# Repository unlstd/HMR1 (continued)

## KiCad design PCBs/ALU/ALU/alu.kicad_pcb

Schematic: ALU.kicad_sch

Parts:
C41, C42, C51, C52, C53, C54, C57, C60, C61, C62, C63, C64, C65, C66, C67, C68, C69, C70, C71, C72, C73, C74, C75, C76, C77, C78, C79, C80, C81, C82, C83, C84, C85, C86, C87, C88, C89, C90, C91, C92, C93, C94, C95, C96, C97, C98: 100nF; C_Disc_D3.0mm_W1.6mm_P2.50mm
J1: ALU_DATA; PinHeader_1x33_P2.54mm_Horizontal
U34: 74LS153; DIP-16_W7.62mm_Socket_LongPads
U35: 74HC138; DIP-16_W7.62mm_Socket_LongPads
U37, U38, U39: 74HC04; DIP-14_W7.62mm_Socket_LongPads
U40, U41, U42, U51, U52, U53, U54, U57, U60: 74HC86; DIP-14_W7.62mm_Socket_LongPads
U61, U62, U63, U64, U88: 74LS08; DIP-14_W7.62mm_Socket_LongPads
U65, U66, U67, U68, U89, U90, U91, U92: 74LS32; DIP-14_W7.62mm_Socket_LongPads
U69, U70, U71, U72, U73, U74, U79, U80, U81, U82, U83, U84, U85, U86: 74HC245; DIP-20_W7.62mm_Socket_LongPads
U75, U76, U77, U78: 74LS283; DIP-16_W7.62mm_Socket_LongPads
U87: 74LS157; DIP-16_W7.62mm_Socket_LongPads

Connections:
+5V: C41.1, C41.2, C42.1, C42.2, C51.1, C51.2, C52.1, C52.2, C53.1, C53.2, C54.1, C54.2, C57.1, C57.2, C60.1, C60.2, C61.1, C61.2, C62.1, C62.2, C63.1, C63.2, C64.1, C64.2, C65.1, C65.2, C66.1, C66.2, C67.1, C67.2, C68.1, C68.2, C69.1, C69.2, C70.1, C70.2, C71.1, C71.2, C72.1, C72.2, C73.1, C73.2, C74.1, C74.2, C75.1, C75.2, C76.1, C76.2, C77.1, C77.2, C78.1, C78.2, C79.1, C79.2, C80.1, C80.2, C81.1, C81.2, C82.1, C82.2, C83.1, C83.2, C84.1, C84.2, C85.1, C85.2, C86.1, C86.2, C87.1, C87.2, C88.1, C88.2, C89.1, C89.2, C90.1, C90.2, C91.1, C91.2, C92.1, C92.2, C93.1, C93.2, C94.1, C94.2, C95.1, C95.2, C96.1, C96.2, C97.1, C97.2, C98.1, C98.2, J1.32, J1.33, U34.1 (Ea), U34.3 (I3a), U34.5 (I1a), U34.6 (I0a), U34.8 (GND), U34.10 (I0b), U34.11 (I1b), U34.12 (I2b), U34.13 (I3b), U34.15 (Eb), U34.16 (VCC), U35.4 (~E0), U35.5 (~E1), U35.6 (E2), U35.8 (GND), U35.16 (VCC), U37.7 (GND), U37.14 (VCC), U38.7 (GND), U38.14 (VCC), U39.7 (GND), U39.14 (VCC), U40.7 (GND), U40.10, U40.12, U40.14 (VCC), U41.7 (GND), U41.14 (VCC), U42.7 (GND), U42.14 (VCC), U51.7 (GND), U51.14 (VCC), U52.7 (GND), U52.14 (VCC), U53.7 (GND), U53.14 (VCC), U54.7 (GND), U54.14 (VCC), U57.7 (GND), U57.14 (VCC), U60.7 (GND), U60.14 (VCC), U61.7 (GND), U61.14 (VCC), U62.7 (GND), U62.14 (VCC), U63.7 (GND), U63.14 (VCC), U64.7 (GND), U64.14 (VCC), U65.7 (GND), U65.14 (VCC), U66.7 (GND), U66.14 (VCC), U67.7 (GND), U67.14 (VCC), U68.7 (GND), U68.14 (VCC), U69.1 (A->B), U69.10 (GND), U69.20 (VCC), U70.1 (A->B), U70.10 (GND), U70.20 (VCC), U71.1 (A->B), U71.10 (GND), U71.20 (VCC), U72.1 (A->B), U72.10 (GND), U72.20 (VCC), U73.1 (A->B), U73.10 (GND), U73.20 (VCC), U74.1 (A->B), U74.10 (GND), U74.20 (VCC), U75.8 (GND), U75.16 (VCC), U76.8 (GND), U76.16 (VCC), U77.8 (GND), U77.16 (VCC), U78.8 (GND), U78.16 (VCC), U79.1 (A->B), U79.10 (GND), U79.20 (VCC), U80.1 (A->B), U80.10 (GND), U80.20 (VCC), U81.1 (A->B), U81.10 (GND), U81.20 (VCC), U82.1 (A->B), U82.10 (GND), U82.20 (VCC), U83.1 (A->B), U83.10 (GND), U83.18 (B0), U83.20 (VCC), U84.1 (A->B), U84.10 (GND), U84.20 (VCC), U85.1 (A->B), U85.10 (GND), U85.20 (VCC), U86.1 (A->B), U86.10 (GND), U86.11 (B7), U86.20 (VCC), U87.5 (I0b), U87.6 (I1b), U87.8 (GND), U87.10 (I1c), U87.11 (I0c), U87.13 (I1d), U87.14 (I0d), U87.15 (E), U87.16 (VCC), U88.7 (GND), U88.14 (VCC), U89.7 (GND), U89.14 (VCC), U90.7 (GND), U90.14 (VCC), U91.7 (GND), U91.14 (VCC), U92.7 (GND), U92.14 (VCC); also elsewhere on the board
/#ALU_A_IN: J1.8; also elsewhere on the board
/#ALU_B_IN: J1.7; also elsewhere on the board
/A Register/O0: U39.9, U60.12, U64.12, U68.12, U75.5 (A1), U86.12 (B6); also elsewhere on the board
/A Register/O1: U39.5, U60.9, U64.9, U68.9, U75.3 (A2), U84.11 (B7), U86.13 (B5); also elsewhere on the board
/A Register/O2: U39.3, U60.4, U64.4, U68.4, U75.14 (A3), U84.12 (B6), U86.14 (B4); also elsewhere on the board
/A Register/O3: U39.1, U60.1, U64.1, U68.1, U75.12 (A4), U84.13 (B5), U86.15 (B3); also elsewhere on the board
/ALU_CARRY_SEL0: J1.5, U34.14 (S0)
/ALU_CARRY_SEL1: J1.4, U34.2 (S1)
/ALU_FR_CARRY: J1.12, U78.9 (C4)
/ALU_FR_OV: J1.9, U40.1, U78.10 (S4), U80.9 (A7), U90.12
/ALU_FR_SIGN: J1.10, U87.4 (Za)
/ALU_FR_ZERO: J1.11, U40.8
/ALU_INV_B: J1.6, U41.1, U41.4, U41.9, U41.12, U42.1, U42.4, U42.9, U42.12, U51.1, U51.4, U51.9, U51.12, U52.1, U52.4, U52.9, U52.12, U87.1 (S)
/ALU_MODE0: J1.3, U35.1 (A0)
/ALU_MODE1: J1.2, U35.2 (A1)
/ALU_MODE2: J1.1, U35.3 (A2)
/B Register/O0: U52.13, U60.13, U64.13, U68.13; also elsewhere on the board
/B Register/O1: U52.10, U60.10, U64.10, U68.10; also elsewhere on the board
/B Register/O2: U52.5, U60.5, U64.5, U68.5; also elsewhere on the board
/B Register/O3: U52.2, U60.2, U64.2, U68.2; also elsewhere on the board
/B Register/O4: U51.13, U57.13, U63.13, U67.13; also elsewhere on the board
/B Register/O5: U51.10, U57.10, U63.10, U67.10; also elsewhere on the board
/B Register/O6: U51.5, U57.5, U63.5, U67.5; also elsewhere on the board
/B Register/O7: U51.2, U57.2, U63.2, U67.2; also elsewhere on the board
/B Register/O8: U42.13, U54.13, U62.13, U66.13; also elsewhere on the board
/B Register/O9: U42.10, U54.10, U62.10, U66.10; also elsewhere on the board
/B Register/O10: U42.5, U54.5, U62.5, U66.5; also elsewhere on the board
/B Register/O11: U42.2, U54.2, U62.2, U66.2; also elsewhere on the board
/B Register/O12: U41.13, U53.13, U61.13, U65.13; also elsewhere on the board
/B Register/O13: U41.10, U53.10, U61.10, U65.10; also elsewhere on the board
/B Register/O14: U41.5, U53.5, U61.5, U65.5; also elsewhere on the board
/B Register/O15: U40.4, U41.2, U53.2, U61.2, U65.2; also elsewhere on the board
/CLK: J1.31; also elsewhere on the board
/D0: J1.14, U70.11 (B7), U72.11 (B7), U74.11 (B7), U79.18 (B0), U82.11 (B7), U84.9 (A7), U86.9 (A7); also elsewhere on the board
/D1: J1.15, U70.12 (B6), U72.12 (B6), U74.12 (B6), U79.17 (B1), U82.12 (B6), U84.8 (A6), U86.8 (A6); also elsewhere on the board
/D2: J1.16, U70.13 (B5), U72.13 (B5), U74.13 (B5), U79.16 (B2), U82.13 (B5), U84.7 (A5), U86.7 (A5); also elsewhere on the board
/D3: J1.17, U70.14 (B4), U72.14 (B4), U74.14 (B4), U79.15 (B3), U82.14 (B4), U84.6 (A4), U86.6 (A4); also elsewhere on the board
/D4: J1.18, U70.15 (B3), U72.15 (B3), U74.15 (B3), U79.14 (B4), U82.15 (B3), U84.5 (A3), U86.5 (A3); also elsewhere on the board
/D5: J1.19, U70.16 (B2), U72.16 (B2), U74.16 (B2), U79.13 (B5), U82.16 (B2), U84.4 (A2), U86.4 (A2); also elsewhere on the board
/D6: J1.20, U70.17 (B1), U72.17 (B1), U74.17 (B1), U79.12 (B6), U82.17 (B1), U84.3 (A1), U86.3 (A1); also elsewhere on the board
/D7: J1.21, U70.18 (B0), U72.18 (B0), U74.18 (B0), U79.11 (B7), U82.18 (B0), U84.2 (A0), U86.2 (A0); also elsewhere on the board
/D8: J1.22, U69.11 (B7), U71.11 (B7), U73.11 (B7), U80.18 (B0), U81.11 (B7), U83.9 (A7), U85.9 (A7); also elsewhere on the board
/D9: J1.23, U69.12 (B6), U71.12 (B6), U73.12 (B6), U80.17 (B1), U81.12 (B6), U83.8 (A6), U85.8 (A6); also elsewhere on the board
/D10: J1.24, U69.13 (B5), U71.13 (B5), U73.13 (B5), U80.16 (B2), U81.13 (B5), U83.7 (A5), U85.7 (A5); also elsewhere on the board
/D11: J1.25, U69.14 (B4), U71.14 (B4), U73.14 (B4), U80.15 (B3), U81.14 (B4), U83.6 (A4), U85.6 (A4); also elsewhere on the board
/D12: J1.26, U69.15 (B3), U71.15 (B3), U73.15 (B3), U80.14 (B4), U81.15 (B3), U83.5 (A3), U85.5 (A3); also elsewhere on the board
/D13: J1.27, U69.16 (B2), U71.16 (B2), U73.16 (B2), U80.13 (B5), U81.16 (B2), U83.4 (A2), U85.4 (A2); also elsewhere on the board
/D14: J1.28, U69.17 (B1), U71.17 (B1), U73.17 (B1), U80.12 (B6), U81.17 (B1), U83.3 (A1), U85.3 (A1); also elsewhere on the board
/D15: J1.29, U69.18 (B0), U71.18 (B0), U73.18 (B0), U80.11 (B7), U81.18 (B0), U83.2 (A0), U85.2 (A0); also elsewhere on the board
/FR_CARRY_IN: J1.13, U34.4 (I2a)
unnamed: U34.7 (Za), U75.7 (C0)
unnamed: U35.15 (~Y0), U79.19 (CE), U80.19 (CE)
unnamed: U35.14 (~Y1), U69.19 (CE), U70.19 (CE)
unnamed: U35.13 (~Y2), U71.19 (CE), U72.19 (CE)
unnamed: U35.12 (~Y3), U73.19 (CE), U74.19 (CE)
unnamed: U35.11 (~Y4), U81.19 (CE), U82.19 (CE)
unnamed: U35.10 (~Y5), U83.19 (CE), U84.19 (CE)
unnamed: U35.9 (~Y6), U85.19 (CE), U86.19 (CE)
unnamed: U40.3, U88.10, U88.12
unnamed: U40.9, U92.8
unnamed: U40.11, U88.9
unnamed: U40.6, U40.13, U88.13
unnamed: U53.3, U69.2 (A0)
unnamed: U53.6, U69.3 (A1)
unnamed: U53.8, U69.4 (A2)
unnamed: U53.11, U69.5 (A3)
unnamed: U54.3, U69.6 (A4)
unnamed: U54.6, U69.7 (A5)
unnamed: U54.8, U69.8 (A6)
unnamed: U54.11, U69.9 (A7)
unnamed: U57.3, U70.2 (A0)
unnamed: U57.6, U70.3 (A1)
unnamed: U57.8, U70.4 (A2)
unnamed: U57.11, U70.5 (A3)
unnamed: U60.3, U70.6 (A4)
unnamed: U60.6, U70.7 (A5)
unnamed: U60.8, U70.8 (A6)
unnamed: U60.11, U70.9 (A7)
unnamed: U61.3, U71.2 (A0)
unnamed: U61.6, U71.3 (A1)
unnamed: U61.8, U71.4 (A2)
unnamed: U61.11, U71.5 (A3)
unnamed: U62.3, U71.6 (A4)
unnamed: U62.6, U71.7 (A5)
unnamed: U62.8, U71.8 (A6)
unnamed: U62.11, U71.9 (A7)
unnamed: U63.3, U72.2 (A0)
unnamed: U63.6, U72.3 (A1)
unnamed: U63.8, U72.4 (A2)
unnamed: U63.11, U72.5 (A3)
unnamed: U64.3, U72.6 (A4)
unnamed: U64.6, U72.7 (A5)
unnamed: U64.8, U72.8 (A6)
unnamed: U64.11, U72.9 (A7)
unnamed: U65.3, U73.2 (A0)
unnamed: U65.6, U73.3 (A1)
unnamed: U65.8, U73.4 (A2)
unnamed: U65.11, U73.5 (A3)
unnamed: U66.3, U73.6 (A4)
unnamed: U66.6, U73.7 (A5)
unnamed: U66.8, U73.8 (A6)
unnamed: U66.11, U73.9 (A7)
unnamed: U67.3, U74.2 (A0)
unnamed: U67.6, U74.3 (A1)
unnamed: U67.8, U74.4 (A2)
unnamed: U67.11, U74.5 (A3)
unnamed: U68.3, U74.6 (A4)
unnamed: U68.6, U74.7 (A5)
unnamed: U68.8, U74.8 (A6)
unnamed: U68.11, U74.9 (A7)
unnamed: U52.11, U75.6 (B1)
unnamed: U52.8, U75.2 (B2)
unnamed: U52.6, U75.15 (B3)
unnamed: U75.9 (C4), U76.7 (C0)
unnamed: U75.4 (S1), U79.2 (A0), U89.2
unnamed: U75.1 (S2), U79.3 (A1), U89.1
unnamed: U75.13 (S3), U79.4 (A2), U89.5
unnamed: U75.10 (S4), U79.5 (A3), U89.4
unnamed: U51.11, U76.6 (B1)
unnamed: U51.8, U76.2 (B2)
unnamed: U51.6, U76.15 (B3)
unnamed: U51.3, U76.11 (B4)
unnamed: U76.9 (C4), U77.7 (C0)
unnamed: U76.4 (S1), U79.6 (A4), U89.10
unnamed: U76.1 (S2), U79.7 (A5), U89.9
unnamed: U76.13 (S3), U79.8 (A6), U89.13
unnamed: U76.10 (S4), U79.9 (A7), U89.12
unnamed: U42.11, U77.6 (B1)
unnamed: U42.8, U77.2 (B2)
unnamed: U42.6, U77.15 (B3)
unnamed: U42.3, U77.11 (B4)
unnamed: U77.9 (C4), U78.7 (C0)
unnamed: U77.4 (S1), U80.2 (A0), U90.2
unnamed: U77.1 (S2), U80.3 (A1), U90.1
unnamed: U77.13 (S3), U80.4 (A2), U90.5
unnamed: U77.10 (S4), U80.5 (A3), U90.4
unnamed: U41.11, U78.6 (B1)
unnamed: U41.8, U78.2 (B2)
unnamed: U41.6, U78.15 (B3)
unnamed: U41.3, U78.11 (B4)
unnamed: U78.4 (S1), U80.6 (A4), U90.10
unnamed: U78.1 (S2), U80.7 (A5), U90.9
unnamed: U78.13 (S3), U80.8 (A6), U90.13
unnamed: U37.2, U81.2 (A0)
unnamed: U37.4, U81.3 (A1)
unnamed: U37.6, U81.4 (A2)
unnamed: U37.8, U81.5 (A3)
unnamed: U37.10, U81.6 (A4)
unnamed: U37.12, U81.7 (A5)
unnamed: U38.2, U81.8 (A6)
unnamed: U38.4, U81.9 (A7)
unnamed: U38.6, U82.2 (A0)
unnamed: U38.8, U82.3 (A1)
unnamed: U38.10, U82.4 (A2)
unnamed: U38.12, U82.5 (A3)
unnamed: U39.2, U82.6 (A4)
unnamed: U39.4, U82.7 (A5)
unnamed: U39.6, U82.8 (A6)
unnamed: U39.8, U82.9 (A7)
unnamed: U87.2 (I0a), U88.8
unnamed: U87.3 (I1a), U88.11
unnamed: U89.3, U91.2
unnamed: U89.6, U91.1
unnamed: U89.8, U91.5
unnamed: U89.11, U91.4
unnamed: U90.3, U91.10
unnamed: U90.6, U91.9
unnamed: U90.8, U91.13
unnamed: U90.11, U91.12
unnamed: U91.3, U92.2
unnamed: U91.6, U92.1
unnamed: U91.8, U92.5
unnamed: U91.11, U92.4
unnamed: U92.6, U92.9
unnamed: U92.3, U92.10

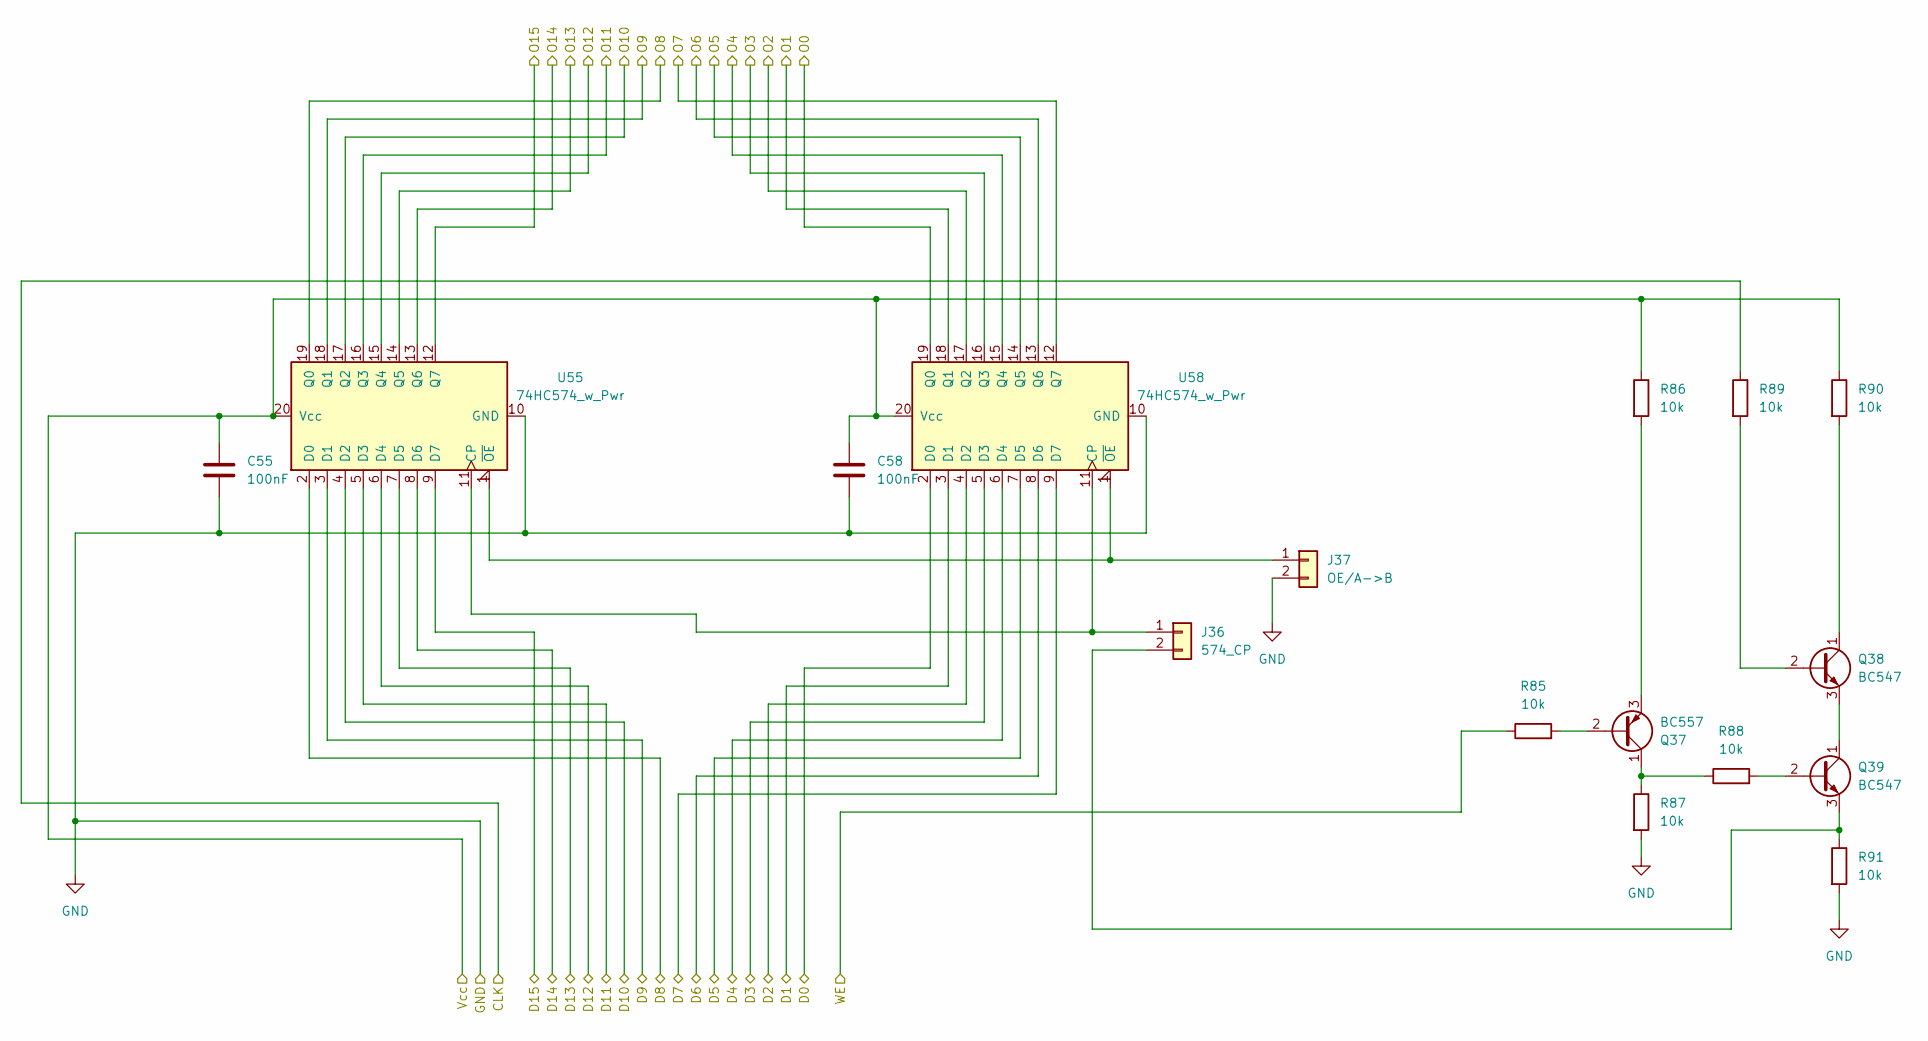
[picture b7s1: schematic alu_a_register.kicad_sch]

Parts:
C55, C58: 100nF; C_Disc_D3.0mm_W1.6mm_P2.50mm
J36: 574_CP; PinHeader_1x02_P2.54mm_Horizontal
J37: OE/A->B; PinHeader_1x02_P2.54mm_Horizontal
Q37: BC557; TO-92_Inline
Q38, Q39: BC547; TO-92_Inline
R85, R86, R87, R88, R89, R90, R91: 10k; R_Axial_DIN0207_L6.3mm_D2.5mm_P10.16mm_Horizontal
U55, U58: 74HC574_w_Pwr; DIP-20_W7.62mm_Socket_LongPads

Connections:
+5V: C55.1, C55.2, C58.1, C58.2, J37.2, R86.1, R87.2, R90.1, R91.2, U55.10 (GND), U55.20 (Vcc), U58.10 (GND), U58.20 (Vcc); also elsewhere on the board
/#ALU_A_IN: R85.1; also elsewhere on the board
/A Register/O0: U58.19 (Q0); also elsewhere on the board
/A Register/O1: U58.18 (Q1); also elsewhere on the board
/A Register/O2: U58.17 (Q2); also elsewhere on the board
/A Register/O3: U58.16 (Q3); also elsewhere on the board
/CLK: R89.1; also elsewhere on the board
/D0: U58.2 (D0); also elsewhere on the board
/D1: U58.3 (D1); also elsewhere on the board
/D2: U58.4 (D2); also elsewhere on the board
/D3: U58.5 (D3); also elsewhere on the board
/D4: U58.6 (D4); also elsewhere on the board
/D5: U58.7 (D5); also elsewhere on the board
/D6: U58.8 (D6); also elsewhere on the board
/D7: U58.9 (D7); also elsewhere on the board
/D8: U55.2 (D0); also elsewhere on the board
/D9: U55.3 (D1); also elsewhere on the board
/D10: U55.4 (D2); also elsewhere on the board
/D11: U55.5 (D3); also elsewhere on the board
/D12: U55.6 (D4); also elsewhere on the board
/D13: U55.7 (D5); also elsewhere on the board
/D14: U55.8 (D6); also elsewhere on the board
/D15: U55.9 (D7); also elsewhere on the board
unnamed: J36.1, U55.11 (CP), U58.11 (CP)
unnamed: J36.2, Q39.3 (E), R91.1
unnamed: J37.1, U55.1 (~OE), U58.1 (~OE)
unnamed: Q37.2 (B), R85.2
unnamed: Q37.1 (C), R87.1, R88.1
unnamed: Q37.3 (E), R86.2
unnamed: Q38.2 (B), R89.2
unnamed: Q38.1 (C), R90.2
unnamed: Q38.3 (E), Q39.1 (C)
unnamed: Q39.2 (B), R88.2

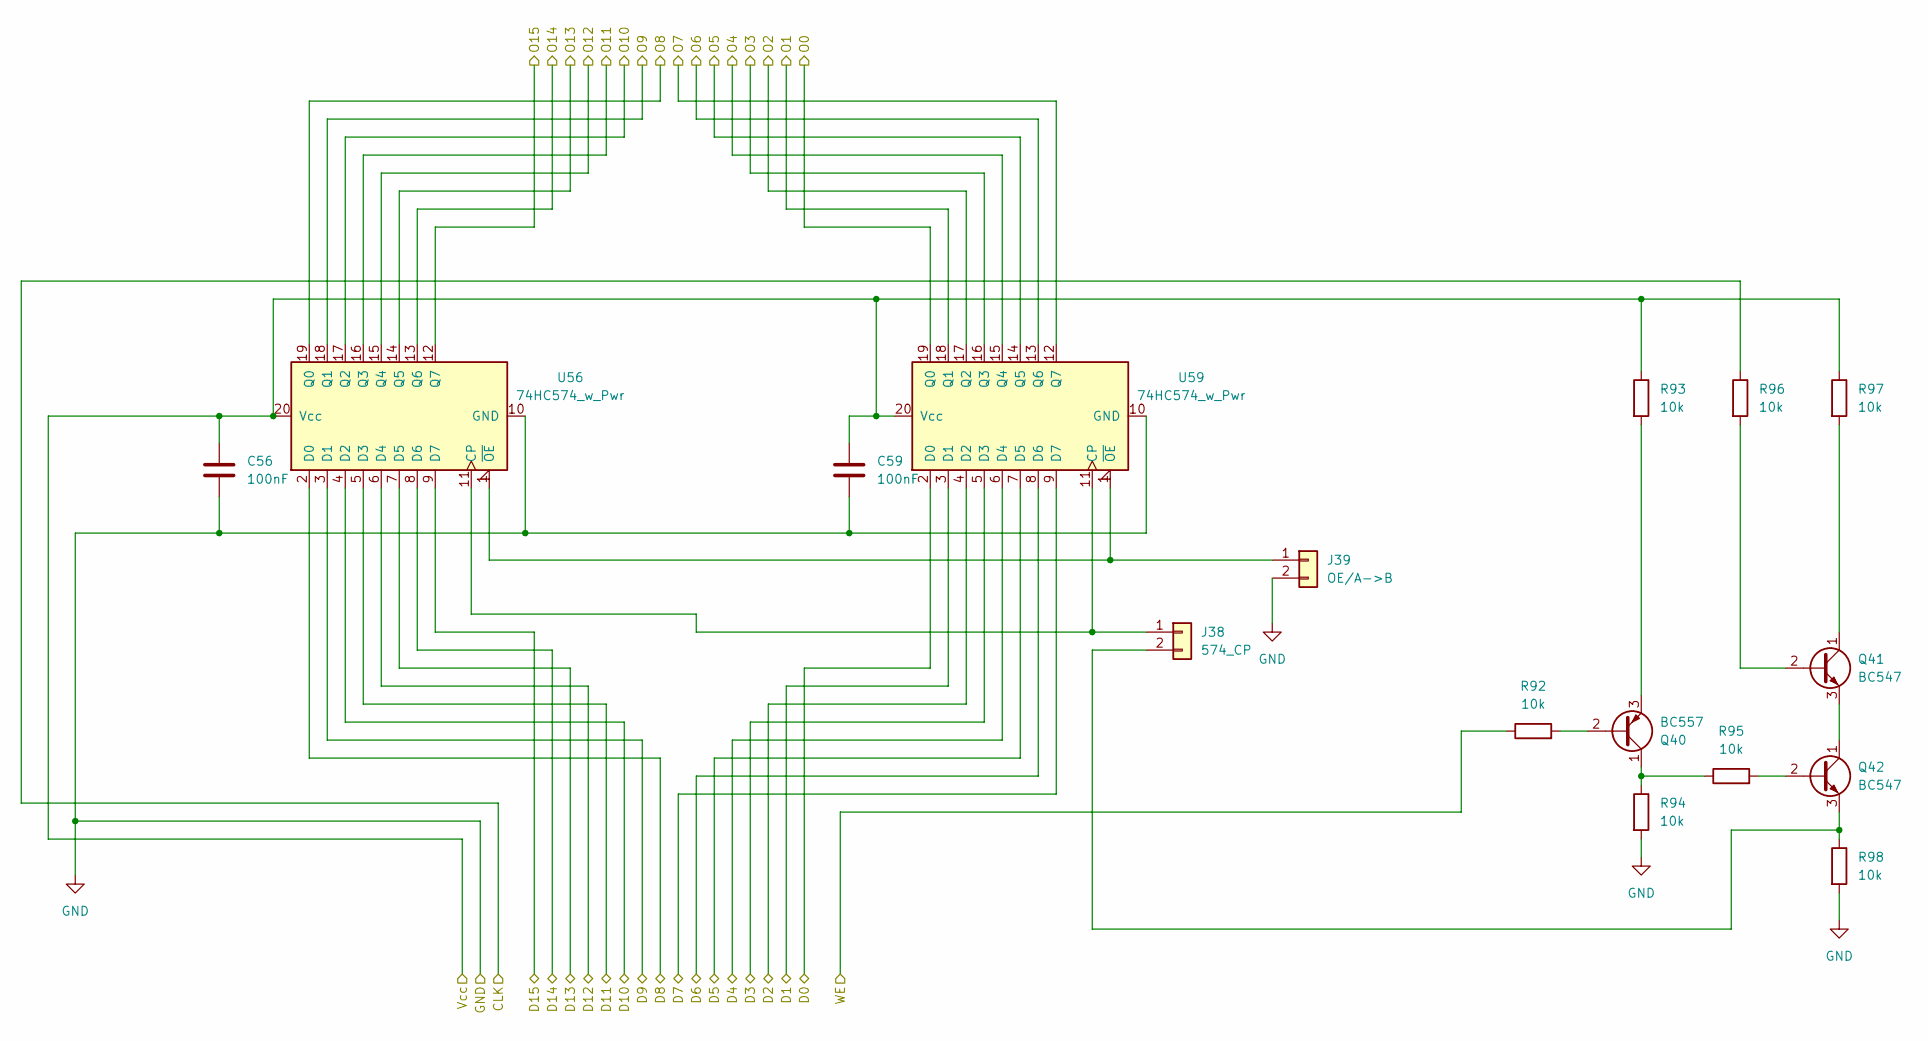
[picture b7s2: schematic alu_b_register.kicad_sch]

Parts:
C56, C59: 100nF; C_Disc_D3.0mm_W1.6mm_P2.50mm
J38: 574_CP; PinHeader_1x02_P2.54mm_Horizontal
J39: OE/A->B; PinHeader_1x02_P2.54mm_Horizontal
Q40: BC557; TO-92_Inline
Q41, Q42: BC547; TO-92_Inline
R92, R93, R94, R95, R96, R97, R98: 10k; R_Axial_DIN0207_L6.3mm_D2.5mm_P10.16mm_Horizontal
U56, U59: 74HC574_w_Pwr; DIP-20_W7.62mm_Socket_LongPads

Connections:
+5V: C56.1, C56.2, C59.1, C59.2, J39.2, R93.1, R94.2, R97.1, R98.2, U56.10 (GND), U56.20 (Vcc), U59.10 (GND), U59.20 (Vcc); also elsewhere on the board
/#ALU_B_IN: R92.1; also elsewhere on the board
/B Register/O0: U59.19 (Q0); also elsewhere on the board
/B Register/O1: U59.18 (Q1); also elsewhere on the board
/B Register/O2: U59.17 (Q2); also elsewhere on the board
/B Register/O3: U59.16 (Q3); also elsewhere on the board
/B Register/O4: U59.15 (Q4); also elsewhere on the board
/B Register/O5: U59.14 (Q5); also elsewhere on the board
/B Register/O6: U59.13 (Q6); also elsewhere on the board
/B Register/O7: U59.12 (Q7); also elsewhere on the board
/B Register/O8: U56.19 (Q0); also elsewhere on the board
/B Register/O9: U56.18 (Q1); also elsewhere on the board
/B Register/O10: U56.17 (Q2); also elsewhere on the board
/B Register/O11: U56.16 (Q3); also elsewhere on the board
/B Register/O12: U56.15 (Q4); also elsewhere on the board
/B Register/O13: U56.14 (Q5); also elsewhere on the board
/B Register/O14: U56.13 (Q6); also elsewhere on the board
/B Register/O15: U56.12 (Q7); also elsewhere on the board
/CLK: R96.1; also elsewhere on the board
/D0: U59.2 (D0); also elsewhere on the board
/D1: U59.3 (D1); also elsewhere on the board
/D2: U59.4 (D2); also elsewhere on the board
/D3: U59.5 (D3); also elsewhere on the board
/D4: U59.6 (D4); also elsewhere on the board
/D5: U59.7 (D5); also elsewhere on the board
/D6: U59.8 (D6); also elsewhere on the board
/D7: U59.9 (D7); also elsewhere on the board
/D8: U56.2 (D0); also elsewhere on the board
/D9: U56.3 (D1); also elsewhere on the board
/D10: U56.4 (D2); also elsewhere on the board
/D11: U56.5 (D3); also elsewhere on the board
/D12: U56.6 (D4); also elsewhere on the board
/D13: U56.7 (D5); also elsewhere on the board
/D14: U56.8 (D6); also elsewhere on the board
/D15: U56.9 (D7); also elsewhere on the board
unnamed: J38.1, U56.11 (CP), U59.11 (CP)
unnamed: J38.2, Q42.3 (E), R98.1
unnamed: J39.1, U56.1 (~OE), U59.1 (~OE)
unnamed: Q40.2 (B), R92.2
unnamed: Q40.1 (C), R94.1, R95.1
unnamed: Q40.3 (E), R93.2
unnamed: Q41.2 (B), R96.2
unnamed: Q41.1 (C), R97.2
unnamed: Q41.3 (E), Q42.1 (C)
unnamed: Q42.2 (B), R95.2

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
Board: 2 copper layers, 125 parts (0 on the bottom side), 209 nets, no tracks yet.

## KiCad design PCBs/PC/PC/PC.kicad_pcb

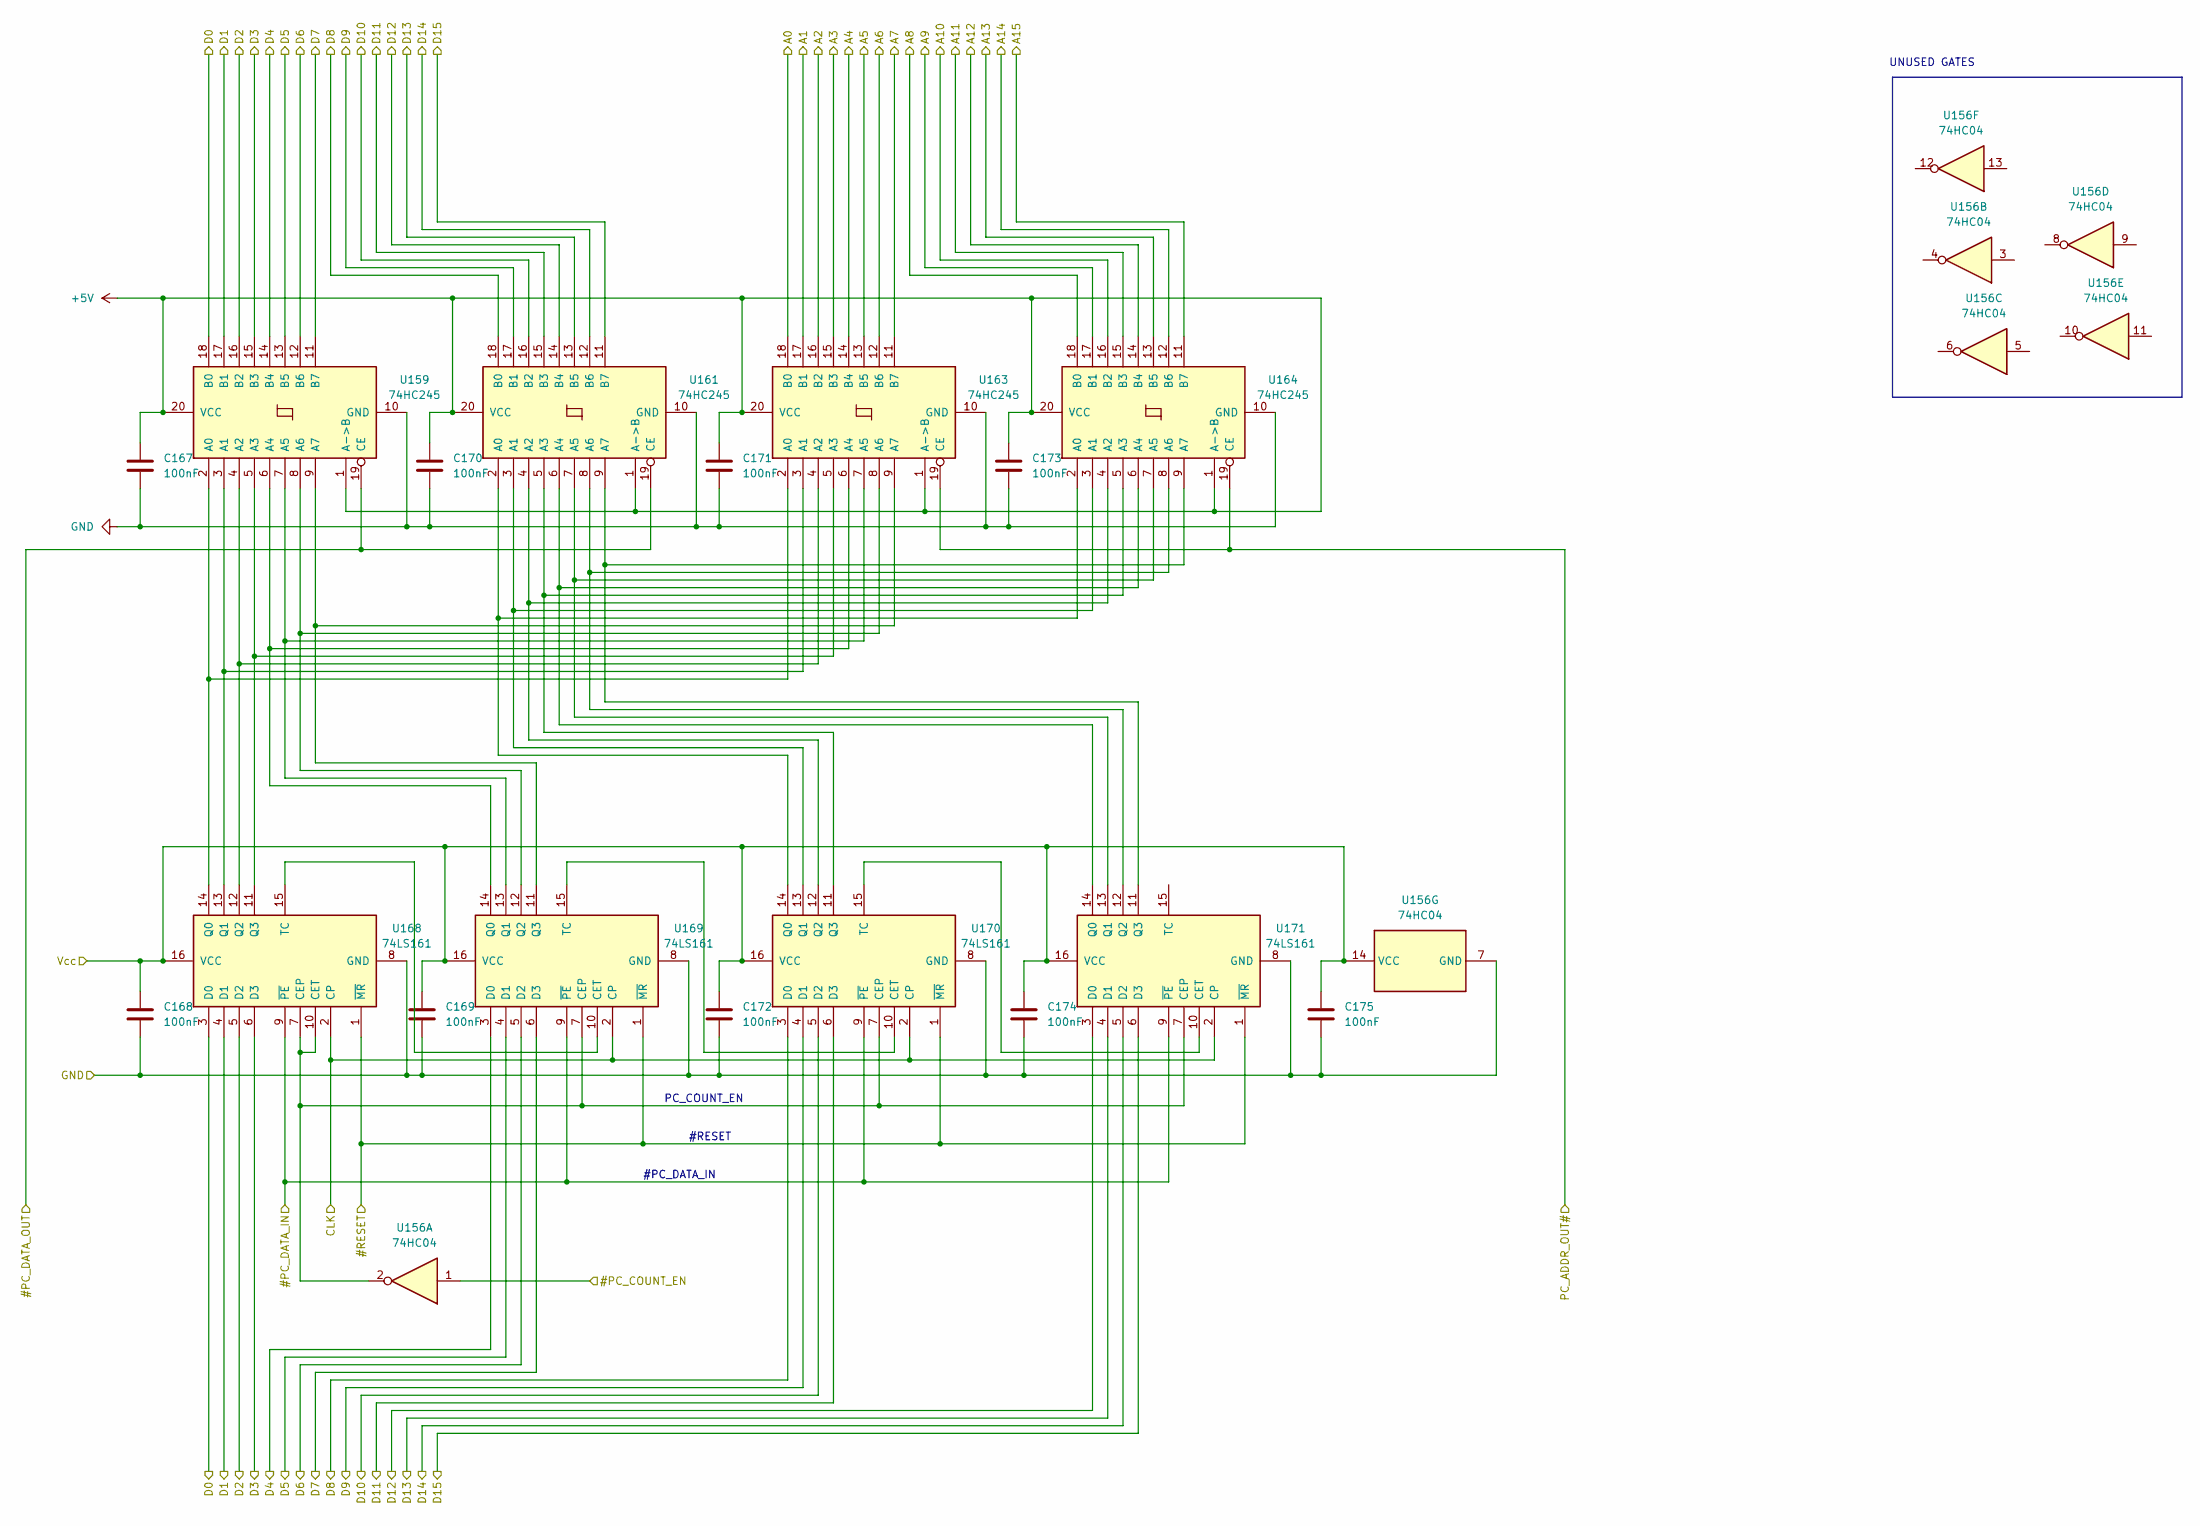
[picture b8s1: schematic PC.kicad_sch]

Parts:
C167, C168, C169, C170, C171, C172, C173, C174, C175: 100nF; C_Disc_D3.0mm_W1.6mm_P2.50mm
U156: 74HC04; DIP-14_W7.62mm_Socket
U159, U161, U163, U164: 74HC245; DIP-20_W7.62mm_Socket
U168, U169, U170, U171: 74LS161; DIP-16_W7.62mm_Socket

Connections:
+5V: C167.1, C168.1, C169.1, C170.1, C171.1, C172.1, C173.1, C174.1, C175.1, U156.14 (VCC), U159.1 (A->B), U159.20 (VCC), U161.1 (A->B), U161.20 (VCC), U163.1 (A->B), U163.20 (VCC), U164.1 (A->B), U164.20 (VCC), U168.16 (VCC), U169.16 (VCC), U170.16 (VCC), U171.16 (VCC); also elsewhere on the board
/#PC_COUNT_EN: U156.1; also elsewhere on the board
/#PC_DATA_IN: U168.9 (~PE), U169.9 (~PE), U170.9 (~PE), U171.9 (~PE); also elsewhere on the board
/#PC_DATA_OUT: U159.19 (CE), U161.19 (CE); also elsewhere on the board
/#RESET: U168.1 (~MR), U169.1 (~MR), U170.1 (~MR), U171.1 (~MR); also elsewhere on the board
/A0: U163.18 (B0); also elsewhere on the board
/A1: U163.17 (B1); also elsewhere on the board
/A2: U163.16 (B2); also elsewhere on the board
/A3: U163.15 (B3); also elsewhere on the board
/A4: U163.14 (B4); also elsewhere on the board
/A5: U163.13 (B5); also elsewhere on the board
/A6: U163.12 (B6); also elsewhere on the board
/A7: U163.11 (B7); also elsewhere on the board
/A8: U164.18 (B0); also elsewhere on the board
/A9: U164.17 (B1); also elsewhere on the board
/A10: U164.16 (B2); also elsewhere on the board
/A11: U164.15 (B3); also elsewhere on the board
/A12: U164.14 (B4); also elsewhere on the board
/A13: U164.13 (B5); also elsewhere on the board
/A14: U164.12 (B6); also elsewhere on the board
/A15: U164.11 (B7); also elsewhere on the board
/CLK: U168.2 (CP), U169.2 (CP), U170.2 (CP), U171.2 (CP); also elsewhere on the board
/D0: U159.18 (B0), U168.3 (D0); also elsewhere on the board
/D1: U159.17 (B1), U168.4 (D1); also elsewhere on the board
/D2: U159.16 (B2), U168.5 (D2); also elsewhere on the board
/D3: U159.15 (B3), U168.6 (D3); also elsewhere on the board
/D4: U159.14 (B4), U169.3 (D0); also elsewhere on the board
/D5: U159.13 (B5), U169.4 (D1); also elsewhere on the board
/D6: U159.12 (B6), U169.5 (D2); also elsewhere on the board
/D7: U159.11 (B7), U169.6 (D3); also elsewhere on the board
/D8: U161.18 (B0), U170.3 (D0); also elsewhere on the board
/D9: U161.17 (B1), U170.4 (D1); also elsewhere on the board
/D10: U161.16 (B2), U170.5 (D2); also elsewhere on the board
/D11: U161.15 (B3), U170.6 (D3); also elsewhere on the board
/D12: U161.14 (B4), U171.3 (D0); also elsewhere on the board
/D13: U161.13 (B5), U171.4 (D1); also elsewhere on the board
/D14: U161.12 (B6), U171.5 (D2); also elsewhere on the board
/D15: U161.11 (B7), U171.6 (D3); also elsewhere on the board
/PC_ADDR_OUT#: U163.19 (CE), U164.19 (CE); also elsewhere on the board
GND: C167.2, C168.2, C169.2, C170.2, C171.2, C172.2, C173.2, C174.2, C175.2, U156.7 (GND), U159.10 (GND), U161.10 (GND), U163.10 (GND), U164.10 (GND), U168.8 (GND), U169.8 (GND), U170.8 (GND), U171.8 (GND); also elsewhere on the board
unnamed: U159.2 (A0), U163.2 (A0), U168.14 (Q0)
unnamed: U159.3 (A1), U163.3 (A1), U168.13 (Q1)
unnamed: U159.4 (A2), U163.4 (A2), U168.12 (Q2)
unnamed: U159.5 (A3), U163.5 (A3), U168.11 (Q3)
unnamed: U159.6 (A4), U163.6 (A4), U169.14 (Q0)
unnamed: U159.7 (A5), U163.7 (A5), U169.13 (Q1)
unnamed: U159.8 (A6), U163.8 (A6), U169.12 (Q2)
unnamed: U159.9 (A7), U163.9 (A7), U169.11 (Q3)
unnamed: U161.2 (A0), U164.2 (A0), U170.14 (Q0)
unnamed: U161.3 (A1), U164.3 (A1), U170.13 (Q1)
unnamed: U161.4 (A2), U164.4 (A2), U170.12 (Q2)
unnamed: U161.5 (A3), U164.5 (A3), U170.11 (Q3)
unnamed: U161.6 (A4), U164.6 (A4), U171.14 (Q0)
unnamed: U161.7 (A5), U164.7 (A5), U171.13 (Q1)
unnamed: U161.8 (A6), U164.8 (A6), U171.12 (Q2)
unnamed: U161.9 (A7), U164.9 (A7), U171.11 (Q3)
unnamed: U156.2, U168.7 (CEP), U168.10 (CET), U169.7 (CEP), U170.7 (CEP), U171.7 (CEP)
unnamed: U168.15 (TC), U169.10 (CET)
unnamed: U169.15 (TC), U170.10 (CET)
unnamed: U170.15 (TC), U171.10 (CET)

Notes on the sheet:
#PC_DATA_IN
#RESET
UNUSED GATES
PC_COUNT_EN

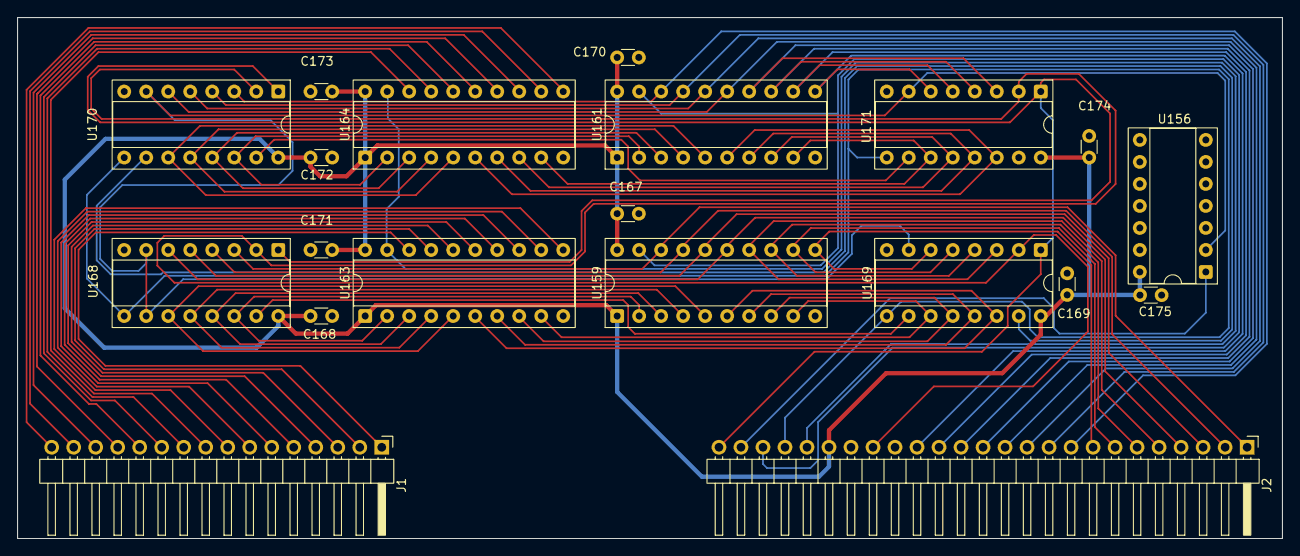
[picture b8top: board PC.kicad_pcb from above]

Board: 2 copper layers, 146.0 x 60.1 mm, 20 parts (0 on the bottom side), 60 nets.

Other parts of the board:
J1: Conn_01x16_Pin; PinHeader_1x16_P2.54mm_Horizontal
J2: Conn_01x25_Pin; PinHeader_1x25_P2.54mm_Horizontal

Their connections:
+5V: J2.20; also elsewhere on the board
/#PC_COUNT_EN: J2.24; also elsewhere on the board
/#PC_DATA_IN: J2.22; also elsewhere on the board
/#PC_DATA_OUT: J2.23; also elsewhere on the board
/#RESET: J2.25; also elsewhere on the board
/A0: J1.1; also elsewhere on the board
/A1: J1.2; also elsewhere on the board
/A2: J1.3; also elsewhere on the board
/A3: J1.4; also elsewhere on the board
/A4: J1.5; also elsewhere on the board
/A5: J1.6; also elsewhere on the board
/A6: J1.7; also elsewhere on the board
/A7: J1.8; also elsewhere on the board
/A8: J1.9; also elsewhere on the board
/A9: J1.10; also elsewhere on the board
/A10: J1.11; also elsewhere on the board
/A11: J1.12; also elsewhere on the board
/A12: J1.13; also elsewhere on the board
/A13: J1.14; also elsewhere on the board
/A14: J1.15; also elsewhere on the board
/A15: J1.16; also elsewhere on the board
/CLK: J2.18; also elsewhere on the board
/D0: J2.1; also elsewhere on the board
/D1: J2.2; also elsewhere on the board
/D2: J2.3; also elsewhere on the board
/D3: J2.4; also elsewhere on the board
/D4: J2.5; also elsewhere on the board
/D5: J2.6; also elsewhere on the board
/D6: J2.7; also elsewhere on the board
/D7: J2.8; also elsewhere on the board
/D8: J2.9; also elsewhere on the board
/D9: J2.10; also elsewhere on the board
/D10: J2.11; also elsewhere on the board
/D11: J2.12; also elsewhere on the board
/D12: J2.13; also elsewhere on the board
/D13: J2.14; also elsewhere on the board
/D14: J2.15; also elsewhere on the board
/D15: J2.16; also elsewhere on the board
/PC_ADDR_OUT#: J2.21; also elsewhere on the board
GND: J2.19; also elsewhere on the board
